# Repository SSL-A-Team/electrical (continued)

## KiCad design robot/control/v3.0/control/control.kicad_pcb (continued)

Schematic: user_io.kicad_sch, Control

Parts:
BZ1: MLT-5020
C32, C33, C34, C35, C36, C37: 0.1uF 63V; C_0402_1005Metric
C38: 4.7uF 25V; C_0805_2012Metric
D9: RBR5LAM60ATR; D_SOD-128
D10, D11, D12, D13: XL-1608UGC-04; LED0603
Q3: SI2310-TP; SOT-23
R84, R85, R86, R89, R90, R92, R93, R94, R95, R97, R107, R114, R115, R117: 330; R_0402_1005Metric
R87, R88, R96, R98, R99, R100, R101, R102, R103, R104, R105, R106, R108, R109, R110, R111, R112, R113, R116, R118: 10k; R_0402_1005Metric
R91: 10; R_0402_1005Metric
SW6: 219-8MST
SW7, SW8, SW9, SW10, SW11, SW12: B3F-1000
U4, U5, U6, U7, U8, U9, U10, U11, U12, U13, U14: SK9822

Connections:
+3V3: BZ1.1 (+), D9.1 (K), R87.2, R88.2, R106.2, R112.2, R113.2, R116.2, SW6.1, SW6.2, SW6.3, SW6.4, SW6.5, SW6.6, SW6.7, SW6.8; also elsewhere on the board
+5V: C38.2, U4.4 (VCC), U5.4 (VCC), U6.4 (VCC), U7.4 (VCC), U8.4 (VCC), U9.4 (VCC), U10.4 (VCC), U11.4 (VCC), U12.4 (VCC), U13.4 (VCC), U14.4 (VCC); also elsewhere on the board
/mcu/BTNS.BACK: R93.2; also elsewhere on the board
/mcu/BTNS.DOWN: R117.2; also elsewhere on the board
/mcu/BTNS.ENTER: R94.2; also elsewhere on the board
/mcu/BTNS.LEFT: R114.2; also elsewhere on the board
/mcu/BTNS.RIGHT: R115.2; also elsewhere on the board
/mcu/BTNS.UP: R107.2; also elsewhere on the board
/mcu/BUZZER: R91.1, R96.1; also elsewhere on the board
/mcu/DIP.0: R84.2; also elsewhere on the board
/mcu/DIP.1: R85.2; also elsewhere on the board
/mcu/DIP.2: R86.2; also elsewhere on the board
/mcu/DIP.3: R89.2; also elsewhere on the board
/mcu/DIP.4: R90.2; also elsewhere on the board
/mcu/DIP.5: R92.2; also elsewhere on the board
/mcu/DIP.6: R95.2; also elsewhere on the board
/mcu/DIP.7: R97.2; also elsewhere on the board
/mcu/DOTSTARS.MOSI: U4.1 (SDI); also elsewhere on the board
/mcu/DOTSTARS.SCK: R118.1, U4.2 (CKI); also elsewhere on the board
/mcu/LEDS.1: R111.1; also elsewhere on the board
/mcu/LEDS.2: R110.1; also elsewhere on the board
/mcu/LEDS.3: R109.1; also elsewhere on the board
/mcu/LEDS.4: R108.1; also elsewhere on the board
GND: C32.2, C33.2, C34.2, C35.2, C36.2, C37.2, C38.1, D10.1 (K), D11.1 (K), D12.1 (K), D13.1 (K), Q3.2 (S), R96.2, R98.1, R99.1, R100.1, R101.1, R102.1, R103.1, R104.1, R105.1, R118.2, SW7.3, SW8.3, SW9.3, SW10.3, SW11.3, SW12.3, U4.3 (GND), U5.3 (GND), U6.3 (GND), U7.3 (GND), U8.3 (GND), U9.3 (GND), U10.3 (GND), U11.3 (GND), U12.3 (GND), U13.3 (GND), U14.3 (GND); also elsewhere on the board
unnamed: BZ1.2 (-), D9.2 (A), Q3.3 (D)
unnamed: C32.1, R87.1, SW7.1
unnamed: C33.1, R88.1, SW8.1
unnamed: C34.1, R106.1, SW9.1
unnamed: C35.1, R112.1, SW10.1
unnamed: C36.1, R113.1, SW11.1
unnamed: C37.1, R116.1, SW12.1
unnamed: D10.2 (A), R108.2
unnamed: D11.2 (A), R109.2
unnamed: D12.2 (A), R110.2
unnamed: D13.2 (A), R111.2
unnamed: Q3.1 (G), R91.2
unnamed: R84.1, R98.2, SW6.16
unnamed: R85.1, R99.2, SW6.15
unnamed: R93.1, SW7.2
unnamed: R94.1, SW8.2
unnamed: R86.1, R100.2, SW6.14
unnamed: R89.1, R101.2, SW6.13
unnamed: R90.1, R102.2, SW6.12
unnamed: R92.1, R103.2, SW6.11
unnamed: R95.1, R104.2, SW6.10
unnamed: R97.1, R105.2, SW6.9
unnamed: R107.1, SW9.2
unnamed: R114.1, SW10.2
unnamed: R115.1, SW11.2
unnamed: R117.1, SW12.2
unnamed: U4.5 (CKO), U5.2 (CKI)
unnamed: U4.6 (SDO), U5.1 (SDI)
unnamed: U5.5 (CKO), U6.2 (CKI)
unnamed: U5.6 (SDO), U6.1 (SDI)
unnamed: U6.5 (CKO), U7.2 (CKI)
unnamed: U6.6 (SDO), U7.1 (SDI)
unnamed: U8.5 (CKO), U9.2 (CKI)
unnamed: U8.6 (SDO), U9.1 (SDI)
unnamed: U9.5 (CKO), U10.2 (CKI)
unnamed: U10.5 (CKO), U11.2 (CKI)
unnamed: U9.6 (SDO), U10.1 (SDI)
unnamed: U10.6 (SDO), U11.1 (SDI)
unnamed: U11.5 (CKO), U12.2 (CKI)
unnamed: U11.6 (SDO), U12.1 (SDI)
unnamed: U13.2 (CKI), U14.5 (CKO)
unnamed: U8.2 (CKI), U13.5 (CKO)
unnamed: U13.1 (SDI), U14.6 (SDO)
unnamed: U8.1 (SDI), U13.6 (SDO)
unnamed: U7.5 (CKO), U14.2 (CKI)
unnamed: U7.6 (SDO), U14.1 (SDI)

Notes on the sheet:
4x Motor 1x Radio 1x IMU 1x Kicker 1x Optical 1x Power 2x General Purpose
Dotstars
Robot Config
Debug Leds
Audio Indicators
User Buttons

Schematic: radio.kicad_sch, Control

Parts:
J5: BM10B-SRSS-TB; JST_SH_BM10B-SRSS-TB_1x10-1MP_P1.00mm_Vertical
R120, R121, R124, R125: 100k; R_0402_1005Metric
R122, R123: 330; R_0402_1005Metric

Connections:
+3V3: J5.9, R120.1, R121.1; also elsewhere on the board
+5V: J5.10; also elsewhere on the board
/mcu/ODIN.BOOT0: J5.7, R124.1; also elsewhere on the board
/mcu/ODIN.CTS: J5.4, R120.2; also elsewhere on the board
/mcu/ODIN.RTS: R123.1; also elsewhere on the board
/mcu/ODIN.RX: J5.5, R121.2; also elsewhere on the board
/mcu/ODIN.TX: R122.1; also elsewhere on the board
/mcu/ODIN.~DET: J5.2; also elsewhere on the board
/mcu/ODIN.~RST: J5.8, R125.1; also elsewhere on the board
GND: J5.1, J5.MP (MountPin), R124.2, R125.2; also elsewhere on the board
unnamed: J5.3, R123.2
unnamed: J5.6, R122.2

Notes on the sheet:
Radio Module Communication

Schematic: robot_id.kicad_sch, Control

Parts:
D3, D4, D6, D7: LTST-C195KGJRKT; LED0606_S_1324
D5: MHT194YBCT; LED0606_Z_1324
D8: XL-1608UOC-06; LED0603
J14: Conn_01x06; JST_GH_BM06B-GHS-TBT_1x06-1MP_P1.25mm_Vertical
R59, R60, R63, R64, R74, R75: 330; R_0402_1005Metric
R61, R62: 2.7k; R_0402_1005Metric
R65, R66, R67, R68, R69, R70, R71, R72, R73, R76, R77, R78, R79, R80, R81, R82, R83: 10k; R_0402_1005Metric
SW4: 221ADC16
SW5: SW_DIP_x02; 219-2MST

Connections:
+3V3: J14.1, R61.2, R62.2, R65.2, R66.2, R73.2, R79.2, R80.2, SW4.C, SW5.1, SW5.2; also elsewhere on the board
/mcu/BOT_ID_DISPLAY.BL: D6.2 (A2), D6.3 (K1); also elsewhere on the board
/mcu/BOT_ID_DISPLAY.BR: D7.2 (A2), D7.3 (K1); also elsewhere on the board
/mcu/BOT_ID_DISPLAY.FL: D3.2 (A2), D3.3 (K1); also elsewhere on the board
/mcu/BOT_ID_DISPLAY.FR: D4.2 (A2), D4.3 (K1); also elsewhere on the board
/mcu/BOT_ID_DISPLAY.SrcDisagree: R83.1; also elsewhere on the board
/mcu/BOT_ID_DISPLAY.TeamBlue: D5.2 (A2), D5.3 (K1); also elsewhere on the board
/mcu/BOT_ID_SWITCHES.IDX0: R64.2; also elsewhere on the board
/mcu/BOT_ID_SWITCHES.IDX1: R63.2; also elsewhere on the board
/mcu/BOT_ID_SWITCHES.IDX2: R60.2; also elsewhere on the board
/mcu/BOT_ID_SWITCHES.IDX3: R59.2; also elsewhere on the board
/mcu/BOT_ID_SWITCHES.SRC_PRIO_USER_~AUTO: R75.2; also elsewhere on the board
/mcu/BOT_ID_SWITCHES.TEAM_BLUE_~YELLOW: R74.2; also elsewhere on the board
/mcu/SHELL_DETECT.LIGHT: J14.5; also elsewhere on the board
/mcu/SHELL_DETECT.RST: J14.4; also elsewhere on the board
/mcu/SHELL_DETECT.SCL: J14.3, R62.1; also elsewhere on the board
/mcu/SHELL_DETECT.SDA: J14.2, R61.1; also elsewhere on the board
GND: D8.1 (K), J14.6, R67.1, R68.1, R69.1, R70.1, R71.1, R72.1, R76.1, R77.1, R78.1, R81.1, R82.1; also elsewhere on the board
unnamed: D3.1 (A1), R65.1
unnamed: D3.4 (K2), R71.2
unnamed: D4.1 (A1), R66.1
unnamed: D4.4 (K2), R72.2
unnamed: D5.1 (A1), R73.1
unnamed: D5.4 (K2), R76.2
unnamed: D6.1 (A1), R79.1
unnamed: D6.4 (K2), R81.2
unnamed: D7.1 (A1), R80.1
unnamed: D7.4 (K2), R82.2
unnamed: D8.2 (A), R83.2
unnamed: R64.1, R70.2, SW4.1
unnamed: R74.1, R77.2, SW5.4
unnamed: R75.1, R78.2, SW5.3
unnamed: R63.1, R69.2, SW4.4 (2)
unnamed: R60.1, R68.2, SW4.3 (4)
unnamed: R59.1, R67.2, SW4.6 (8)

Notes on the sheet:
Disagreement Warning
Dot Pattern Preview
Robot ID Selection
Shell ID Board Connector
Team Selection

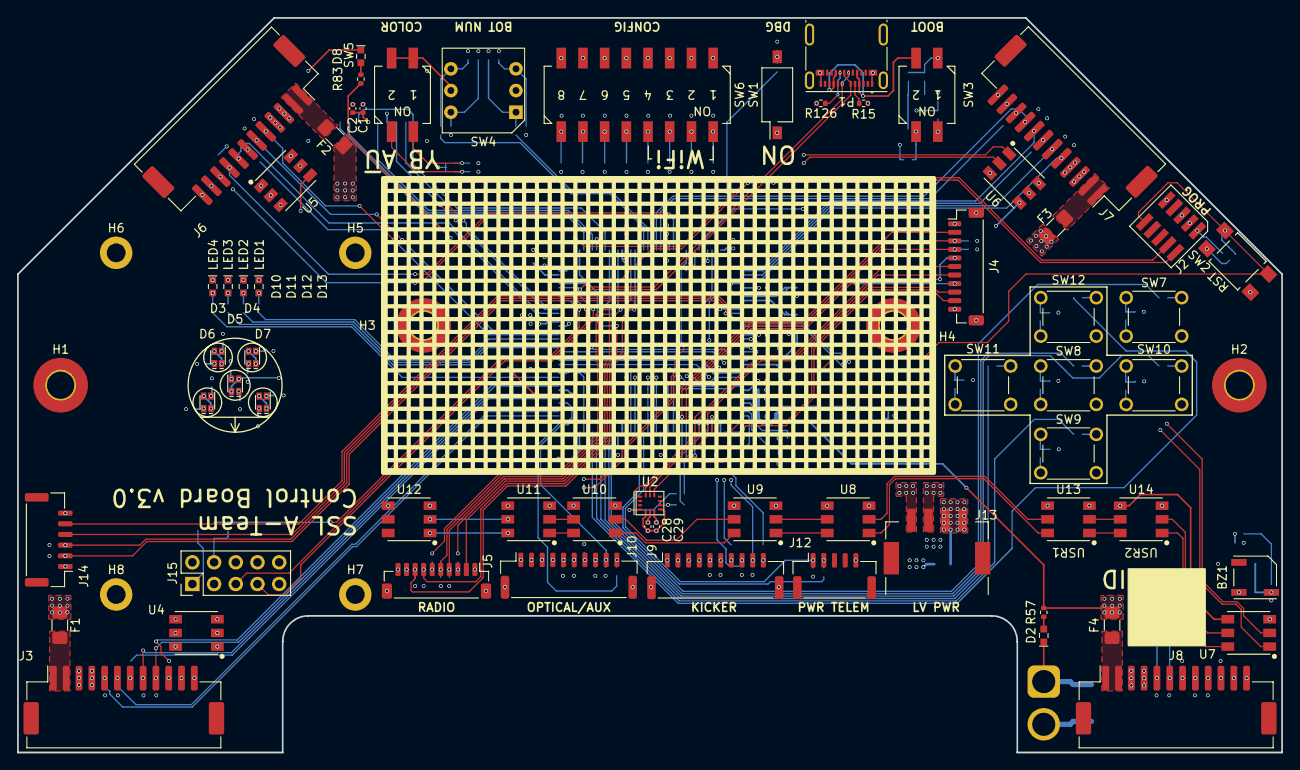
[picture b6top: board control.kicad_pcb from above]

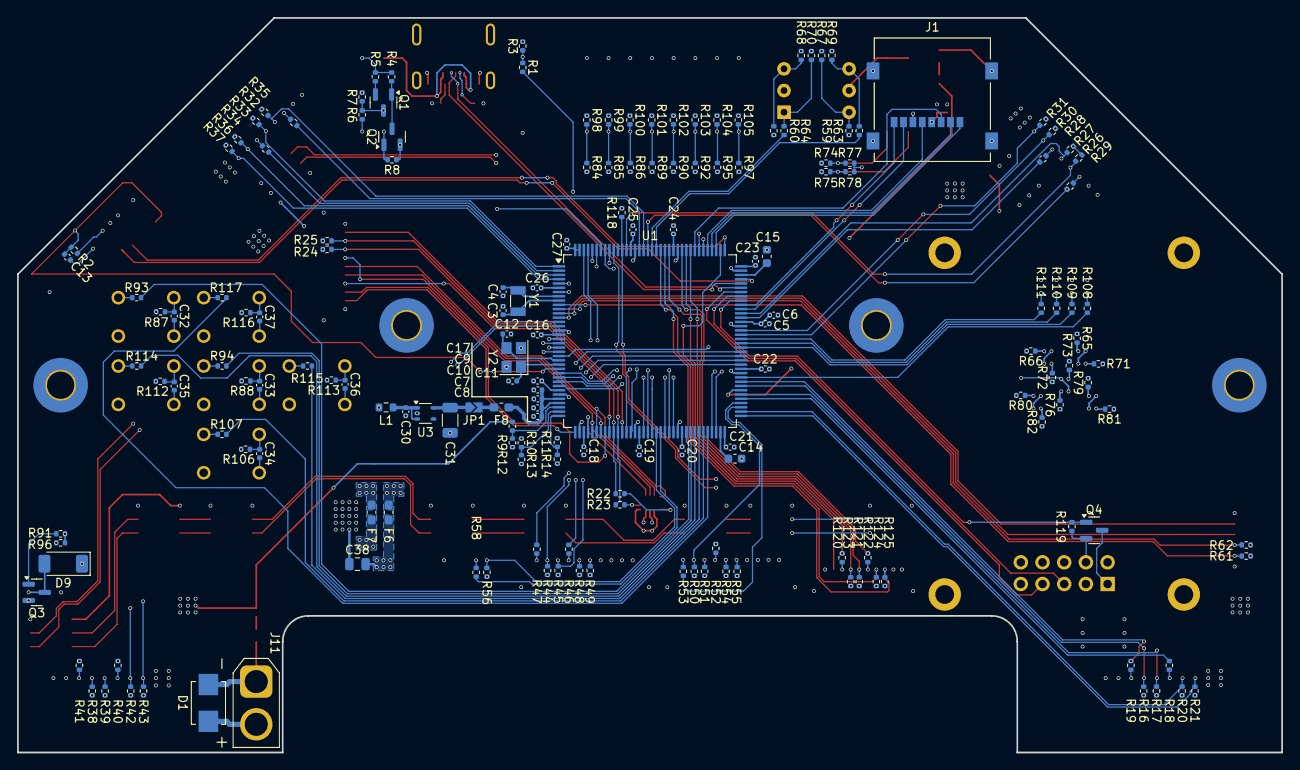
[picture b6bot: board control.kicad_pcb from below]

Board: 6 copper layers, 148.0 x 86.0 mm, 243 parts (173 on the bottom side), 221 nets.

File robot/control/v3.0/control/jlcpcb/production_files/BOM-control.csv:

Comment,Designator,Footprint,LCSC,Quantity
1k,"R12,R13,R14,R5,R6",R_0402_1005Metric,C11702,5
SMBJ26CA,D1,D_SMB_Non-Polar,C123932,1
LTST-C195KGJRKT,"D3,D4,D6,D7",LED0606_S_1324,C125104,4
USB_C_Plug_USB2.0,P1,USB_C_Receptacle_Molex_105450-0101,C134092,1
1u 50V,"C2,C6,C8,C9",C_0402_1005Metric,C1518208,4
650 @100MHz,L1,R_0603_1608Metric,C15402,1
15pF,"C3,C4",C_0402_1005Metric,C1548,2
2.2uF 10V,"C14,C15",C_0603_1608Metric,C1607,2
11pF,"C11,C12",C_0402_1005Metric,C161525,2
0.1uF 63V,"C28,C29,C30,C32,C33,C34,C35,C36,C37",C_0402_1005Metric,C162178,9
4.7uF 25V,C38,C_0805_2012Metric,C1779,1
1u,C31,C_1206_3216Metric,C1848,1
Conn_01x06,J14,JST_GH_BM06B-GHS-TBT_1x06-1MP_P1.25mm_Vertical,C189892,1
JST-GH-SM05B,J12,JST_GH_SM05B-GHS-TB_1x05-1MP_P1.25mm_Horizontal,C189896,1
10,R91,R_0402_1005Metric,C25077,1
330,"R1,R107,R114,R115,R117,R122,R123,R18,R19,R22,R23,R28,R29,R34,R35,R40,R41,R46,R47,R52,R53,R58,R59,R60,R63,R64,R74,R75,R84,R85,R86,R89,R90,R92,R93,R94,R95,R97",R_0402_1005Metric,C25104,38
BSS138K,"Q2,Q4",SOT-23,C255592,2
100k,"R119,R120,R121,R124,R125,R16,R17,R20,R21,R26,R27,R30,R31,R32,R33,R36,R37,R38,R39,R4,R42,R43,R44,R45,R48,R49,R50,R51,R54,R55,R56,R7,R8",R_0402_1005Metric,C25741,33
10k,"R100,R101,R102,R103,R104,R105,R106,R108,R109,R110,R111,R112,R113,R116,R118,R24,R25,R3,R65,R66,R67,R68,R69,R70,R71,R72,R73,R76,R77,R78,R79,R80,R81,R82,R83,R87,R88,R96,R98,R99",R_0402_1005Metric,C25744,40
1.5k,R10,R_0402_1005Metric,C25867,1
2.7k,"R61,R62",R_0402_1005Metric,C25885,2
5.1k,"R126,R15",R_0402_1005Metric,C25905,2
Conn_01x04,J13,JST_PA_SM04B-PASS_1x04_P2.00mm_Horizontal,C265073,1
BM10B-SRSS-TB,J5,JST_SH_BM10B-SRSS-TB_1x10-1MP_P1.00mm_Vertical,C265443,1
Conn_01x10_MountingPin,"J10,J9",JST_GH_SM10B-GHS-TB_1x10-1MP_P1.25mm_Horizontal,C2683602,2
11.5k,R9,R_0402_1005Metric,C270653,1
MHT194YBCT,D5,LED0606_Z_1324,C2764891,1
SK9822,"U10,U11,U12,U13,U14,U4,U5,U6,U7,U8,U9",SK9822,C2829089,11
219-8MST,SW6,219-8MST,C2842674,1
RST,SW2,SW_SPST_TL3305A,C2886902,1
~,"F6,F7",Fuse_0603_1608Metric_Pad1.05x0.95mm_HandSolder,C2924957,2
SW_DIP_x02,SW3,219-2MST,C2961978,1
SW_DIP_x02,SW5,219-2MST,C314502,1
23.7k,R57,R_0402_1005Metric,C327362,1
06F-0200L1,F8,Fuse_0603_1608Metric_Pad1.05x0.95mm_HandSolder,C377220,1
TAXM8M4RDBCCT2T,Y2,Crystal_SMD_3225-4Pin_3.2x2.5mm,C400090,1
Conn_ARM_JTAG_SWD_10,J2,Samtec-2x5pin-1.27mm,C448647,1
RBR5LAM60ATR,D9,D_SOD-128,C509955,1
TLV70030_SOT353,U3,SOT-353_SC-70-5,C527437,1
BMI323,U2,BMI323,C5368700,1
4A,"F1,F2,F3,F4",Fuse_1206_3216Metric_Pad1.42x1.75mm_HandSolder,C5383193,4
A6SN-1104,SW1,SW_DIP_SPSTx01_Slide_Omron_A6S-110x_W8.9mm_P2.54mm,C600988,1
SI2310-TP,Q3,SOT-23,C669000,1
STM32H723ZGTx,U1,LQFP-144_20x20mm_P0.5mm,C730146,1
100n 50V,"C1,C10,C13,C16,C17,C18,C19,C20,C21,C22,C23,C24,C25,C26,C27,C5,C7",C_0402_1005Metric,C77020,17
650,R11,R_0402_1005Metric,C82294,1
Q13FC13500005,Y1,Crystal_SMD_3215-2Pin_3.2x1.5mm,C841881,1
BSS84,Q1,SOT-23,C85202,1
B3F-1000,"SW10,SW11,SW12,SW7,SW8,SW9",B3F-1000,C93157,6
MLT-5020,BZ1,MLT-5020,C95297,1
XL-1608UOC-06,D8,LED0603,C965800,1
XL-1608UGC-04,"D10,D11,D12,D13",LED0603,C965804,4
XL-1608UWC-04,D2,LED0603,C965808,1
SM12B-ZESS,J6,JST_ZE_SM12B-ZESS-TB_1x12-1MP_P1.50mm_Horizontal,,1
221ADC16,SW4,221ADC16,,1
SM12B-ZESS,J8,JST_ZE_SM12B-ZESS-TB_1x12-1MP_P1.50mm_Horizontal,,1
SM12B-ZESS,J3,JST_ZE_SM12B-ZESS-TB_1x12-1MP_P1.50mm_Horizontal,,1
SM12B-ZESS,J7,JST_ZE_SM12B-ZESS-TB_1x12-1MP_P1.50mm_Horizontal,,1
BM11B-SRSS-TB,J4,JST_SH_BM11B-SRSS-TB_1x11-1MP_P1.00mm_Vertical,,1
Conn_02x05_Odd_Even,J15,PinHeader_2x05_P2.54mm_Vertical,,1
MEM2067-02-180-00-A,J1,MEM2067-02-180-00-A,,1

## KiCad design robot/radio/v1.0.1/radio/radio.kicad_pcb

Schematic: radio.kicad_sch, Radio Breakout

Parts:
C1, C2, C10, C11: 10u 10v; C_0603_1608Metric
C3: 1u 10v; C_0603_1608Metric
C4: 0.1u 10v; C_0603_1608Metric
C5, C6, C7, C8, C9: 0.1u; C_0603_1608Metric
D1: 150141m173100; LED_RGB_Wuerth-PLCC4_3.2x2.8mm_150141M173100
H1, H2: MountingHole; MountingHole_3.2mm_M3
J1: Conn_01x10; JST_SH_SM10B-SRSS-TB_1x10-1MP_P1.00mm_Horizontal
JP1: SW1; SolderJumper-2_2.0x1.2mm_Open
JP2: SW0; SolderJumper-2_2.0x1.2mm_Open
JP3: RTS Source Select; SolderJumper-3_P1.3mm_Open_RoundedPad1.0x1.5mm
JP4: CTS Source Select; SolderJumper-3_P1.3mm_Open_RoundedPad1.0x1.5mm
Q1: BSS138K; SOT-23
R1, R3: 1k; R_0603_1608Metric
R2: 2K7; R_0603_1608Metric
R4, R5: 330; R_0603_1608Metric
R6, R7, R8, R9, R10: 10k; R_0603_1608Metric
SW1: SPST_12-34; TS02-66-73-BK-160-SCR-D
U1: 74LVC3G07; VSSOP-8_2.3x2mm_P0.5mm
U2: ODIN-W26x; ODIN_W2
U3: TXS0108EPW; TSSOP-20_4.4x6.5mm_P0.65mm

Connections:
+1V8: C5.2, C7.2, R6.2, R10.2, U1.8 (VCC), U2.A2 (V_INT), U3.2 (VCCA)
+3V3: C1.2, C2.2, C3.2, C4.2, C6.2, C10.2, C11.2, D1.1 (A), J1.9, U2.A4 (VCC), U3.19 (VCCB)
+5V: J1.10
/BLUE: U1.1, U2.A9 (BLUE)
/BLUE_B: R3.1, U1.7
/BOOT0_3v3: J1.7
/GRN_B: R2.1, U1.2
/GRN_SW1: R4.2, U1.6, U2.A8 (GREEN/SWITCH_1)
/LED_B_CL: D1.2 (BK), R3.2
/LED_G_CL: D1.4 (GK), R2.2
/LED_R_CL: D1.3 (RK), R1.2
/RADIO_CTS_3v3: JP4.2 (C), U3.18 (B2)
/RADIO_RTS_3v3: JP3.2 (C), U3.20 (B1)
/RED: U1.3, U2.A7 (RED)
/RED_B: R1.1, U1.5
/RESET_N: C9.2, Q1.3 (D), SW1.1, U2.A1 (RESET_N)
/RST_3v3: J1.8, Q1.1 (G), R8.2
/SW0: R5.1, U2.A6 (SWITCH_0)
/UART_CTS_1v8: U2.A10 (UART_CTS), U3.3 (A2)
/UART_CTS_3v3: J1.4, JP3.1 (A), JP4.1 (A)
/UART_RTS_1v8: U2.A12 (UART_RTS), U3.1 (A1)
/UART_RTS_3v3: J1.3, JP3.3 (B), JP4.3 (B)
/UART_RX_1v8: U2.A13 (UART_RXD), U3.4 (A3)
/UART_RX_3v3: J1.6, U3.17 (B3)
/UART_TX_1v8: U2.A11 (UART_TXD), U3.5 (A4)
/UART_TX_3v3: J1.5, U3.16 (B4)
GND: C1.1, C2.1, C3.1, C4.1, C5.1, C6.1, C7.1, C8.2, C9.1, C10.1, C11.1, J1.1, J1.2, JP1.2 (B), JP2.2 (B), Q1.2 (S), R6.1, R7.1, R8.1, R9.1, SW1.4, U1.4 (GND), U2.A3 (GND), U2.C1 (GND), U2.C3 (GND), U2.C4 (GND), U2.C7 (GND), U2.D7 (GND), U2.G1 (GND), U2.G2 (GND), U2.G3 (GND), U2.G4 (GND), U2.G5 (GND), U2.G6 (GND), U2.G7 (GND), U2.G8 (GND), U2.G9 (GND), U2.G10 (GND), U2.G11 (GND), U2.G12 (GND), U2.G13 (GND), U2.G14 (GND), U2.G15 (GND), U2.G16 (GND), U2.G17 (GND), U2.G18 (GND), U2.G19 (GND), U2.G20 (GND), U2.G21 (GND), U2.G22 (GND), U2.G23 (GND), U2.G24 (GND), U2.G25 (GND), U2.G26 (GND), U2.G27 (GND), U2.G28 (GND), U2.G29 (GND), U2.G30 (GND), U2.G31 (GND), U2.G32 (GND), U2.G33 (GND), U2.G34 (GND), U2.G35 (GND), U2.G36 (GND), U2.G37 (GND), U2.G38 (GND), U2.G39 (GND), U3.11 (GND)
unnamed: JP1.1 (A), R4.1
unnamed: JP2.1 (A), R5.2
unnamed: R7.2, U3.6 (A5), U3.7 (A6), U3.8 (A7), U3.9 (A8)
unnamed: R9.2, U3.12 (B8), U3.13 (B7), U3.14 (B6), U3.15 (B5)
unnamed: C8.1, R10.1, U3.10 (OE)

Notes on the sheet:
Radio Ground
~{DET}
Radio Pinout
Green signal will not be valid until 500ms after startup
Level Shifter
Board Reset
Decoupling cap for 74LVC
Status LEDs
UART/Firmware Reset
Bridge SW1 and power on to restore UART defaults Bridge SW1 and SW0 and power on for 10s to restore all factory defaults

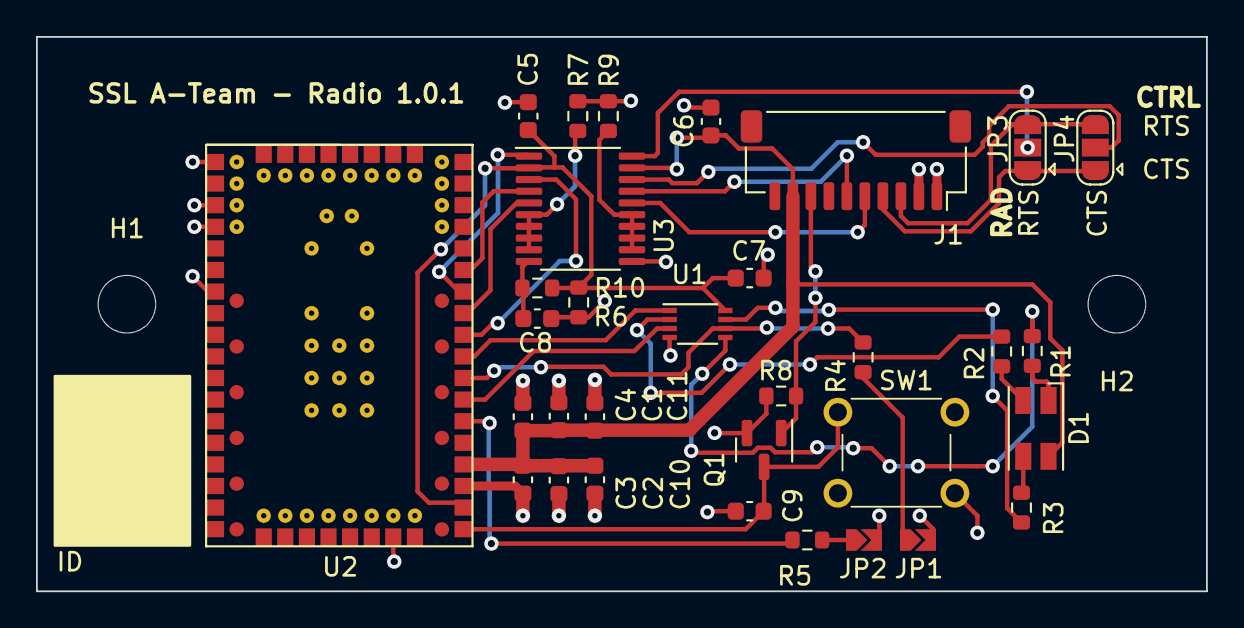
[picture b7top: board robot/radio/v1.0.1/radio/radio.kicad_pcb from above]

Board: 2 copper layers, 65.0 x 30.8 mm, 34 parts (0 on the bottom side), 30 nets.

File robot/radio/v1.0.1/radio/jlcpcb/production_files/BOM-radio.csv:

Comment,Designator,Footprint,LCSC,Quantity
74LVC3G07,U1,VSSOP-8_2.3x2mm_P0.5mm,C131955,1
0.1u 10v,"C4,C5,C6,C7,C8,C9",C_0603_1608Metric,C1591,6
Conn_01x10,J1,JST_SH_SM10B-SRSS-TB_1x10-1MP_P1.00mm_Horizontal,C160409,1
TXS0108EPW,U3,TSSOP-20_4.4x6.5mm_P0.65mm,C17206,1
10u 10v,"C1,C10,C11,C2",C_0603_1608Metric,C19702,4
1k,"R1,R3",R_0603_1608Metric,C21190,2
330,"R4,R5",R_0603_1608Metric,C23138,2
BSS138K,Q1,SOT-23,C255592,1
10k,"R10,R6,R7,R8,R9",R_0603_1608Metric,C25804,5
1u 10v,C3,C_0603_1608Metric,C26413,1
2K7,R2,R_0603_1608Metric,C328353,1
150141m173100,D1,LED_RGB_Wuerth-PLCC4_3.2x2.8mm_150141M173100,C5342281,1

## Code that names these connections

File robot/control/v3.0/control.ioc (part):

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Mcu.Name=STM32H723ZGTx
Mcu.Package=LQFP144
Mcu.UserName=STM32H723ZGTx
PA0.GPIOParameters=GPIO_Label
PA0.GPIO_Label=ADC1_INP16_VBATT
PA0.Mode=IN16-Single-Ended
PA0.Signal=ADC1_INP16
PA1.GPIOParameters=GPIO_Label
PA1.GPIO_Label=ADC1_INP17_5v0
PA1.Mode=IN17-Single-Ended
PA1.Signal=ADC1_INP17
PA10.GPIOParameters=GPIO_Label
PA10.GPIO_Label=USART1_RX_DISPLAY
PA10.Mode=Asynchronous
PA10.Signal=USART1_RX
PA11.Mode=Device_Only_FS
PA11.Signal=USB_OTG_HS_DM
PA12.Mode=Device_Only_FS
PA12.Signal=USB_OTG_HS_DP
PA13(JTMS/SWDIO).Mode=Serial_Wire
PA13(JTMS/SWDIO).Signal=DEBUG_JTMS-SWDIO
PA14(JTCK/SWCLK).Mode=Serial_Wire
PA14(JTCK/SWCLK).Signal=DEBUG_JTCK-SWCLK
PA15(JTDI).GPIOParameters=GPIO_Label
PA15(JTDI).GPIO_Label=PA15_RADIO_nDET
PA15(JTDI).Signal=GPIO_Input
PA2.GPIOParameters=GPIO_Label
PA2.GPIO_Label=ADC1_INP14_3v3
PA2.Signal=ADCx_INP14
PA3.GPIOParameters=GPIO_Label
PA3.GPIO_Label=PA3_IMU_NSS1
PA3.Signal=GPIO_Output
PA4.GPIOParameters=GPIO_Label
PA4.GPIO_Label=SPI1_NSS0_IMU
PA4.Mode=NSS_Signal_Hard_Input
PA4.Signal=SPI1_NSS
PA5.GPIOParameters=GPIO_Label
PA5.GPIO_Label=SPI1_SCK_IMU
PA5.Mode=Full_Duplex_Master
PA5.Signal=SPI1_SCK
PA6.GPIOParameters=GPIO_Label
PA6.GPIO_Label=SPI1_MISO_IMU
PA6.Mode=Full_Duplex_Master
PA6.Signal=SPI1_MISO
PA7.GPIOParameters=GPIO_Label
PA7.GPIO_Label=SPI1_MOSI_IMU
PA7.Mode=Full_Duplex_Master
PA7.Signal=SPI1_MOSI
PA8.GPIOParameters=GPIO_Label
PA8.GPIO_Label=O_DISPLAY_RST
PA8.Signal=GPIO_Output
PA9.GPIOParameters=GPIO_Label
PA9.GPIO_Label=USART1_TX_DISPLAY
PA9.Mode=Asynchronous
PA9.Signal=USART1_TX
PB0.GPIOParameters=GPIO_Label
PB0.GPIO_Label=EXTI0_IMU_INT1
PB0.Signal=GPXTI0
PB1.GPIOParameters=GPIO_Label
PB1.GPIO_Label=EXTI1_IMU_INT2
PB1.Signal=GPXTI1
PB10.GPIOParameters=GPIO_Label
PB10.GPIO_Label=BOT_ID_TEAM
PB10.Signal=GPIO_Input
PB11.GPIOParameters=GPIO_Label
PB11.GPIO_Label=BOT_ID_SRC_PRIO
PB11.Signal=GPIO_Input
PB12.GPIOParameters=GPIO_Label
PB12.GPIO_Label=PB12_MOTOR_FR_BOOT0
PB12.Signal=GPIO_Output
PB13.GPIOParameters=GPIO_Label
PB13.GPIO_Label=PB13_MOTOR_FR_RST
PB13.Signal=GPIO_Output
PB14.GPIOParameters=GPIO_Label
PB14.GPIO_Label=UART4_RTS_FLOWCONTROL
PB14.Mode=CTS_RTS
PB14.Signal=UART4_RTS
PB15.GPIOParameters=GPIO_Label
PB15.GPIO_Label=UART4_CTS_FLOWCONTROL
PB15.Mode=CTS_RTS
PB15.Signal=UART4_CTS
PB2.GPIOParameters=GPIO_Label
PB2.GPIO_Label=PB2_IMU_NDET
PB2.Signal=GPIO_Input
PB3(JTDO/TRACESWO).GPIOParameters=GPIO_Label
PB3(JTDO/TRACESWO).GPIO_Label=SPI6_SCK_DOTSTAR
PB3(JTDO/TRACESWO).Mode=Full_Duplex_Master
PB3(JTDO/TRACESWO).Signal=SPI6_SCK
PB4(NJTRST).GPIOParameters=GPIO_Label
PB4(NJTRST).GPIO_Label=SPI6_MISO_DOTSTAR
PB4(NJTRST).Mode=Full_Duplex_Master
PB4(NJTRST).Signal=SPI6_MISO
PB5.GPIOParameters=GPIO_Label
PB5.GPIO_Label=SPI6_MOSI_DOTSTAR
PB5.Mode=Full_Duplex_Master
PB5.Signal=SPI6_MOSI
PB6.GPIOParameters=GPIO_Label
PB6.GPIO_Label=PB7_FLOWCONTROL_RST
PB6.Signal=GPIO_Output
PB7.GPIOParameters=GPIO_Label
PB7.GPIO_Label=PB7_FLOWCONTROL_BOOT0
PB7.Signal=GPIO_Output
PB8.GPIOParameters=GPIO_Label
PB8.GPIO_Label=UART4_RX_FLOWCONTROL
PB8.Mode=Asynchronous
PB8.Signal=UART4_RX
PB9.GPIOParameters=GPIO_Label
PB9.GPIO_Label=UART4_TX_FLOWCONTROL
PB9.Mode=Asynchronous
PB9.Signal=UART4_TX
PC0.GPIOParameters=GPIO_Label
PC0.GPIO_Label=BOT_ID_IND_FL
PC0.Signal=GPIO_Output
PC1.GPIOParameters=GPIO_Label
PC1.GPIO_Label=BOT_ID_IND_FR
PC1.Signal=GPIO_Output
PC10.Mode=SD_4_bits_Wide_bus
PC10.Signal=SDMMC1_D2
PC11.Mode=SD_4_bits_Wide_bus
PC11.Signal=SDMMC1_D3
PC12.Mode=SD_4_bits_Wide_bus
PC12.Signal=SDMMC1_CK
PC13.GPIOParameters=GPIO_Label
PC13.GPIO_Label=DIP_DEBUG_MODE
PC13.Signal=GPIO_Input
PC14-OSC32_IN.Mode=LSE-External-Oscillator
PC14-OSC32_IN.Signal=RCC_OSC32_IN
PC15-OSC32_OUT.Mode=LSE-External-Oscillator
PC15-OSC32_OUT.Signal=RCC_OSC32_OUT
PC2_C.GPIOParameters=GPIO_Label
PC2_C.GPIO_Label=BOT_ID_IND_BL
PC2_C.Signal=GPIO_Output
PC3_C.GPIOParameters=GPIO_Label
PC3_C.GPIO_Label=BOT_ID_IND_BR
PC3_C.Signal=GPIO_Output
PC4.GPIOParameters=GPIO_Label
PC4.GPIO_Label=PC4_IMU_NSS2
PC4.Signal=GPIO_Output
PC5.GPIOParameters=GPIO_Label
PC5.GPIO_Label=PC5_IMU_NSS3
PC5.Signal=GPIO_Output
PC6.GPIOParameters=GPIO_Label
PC6.GPIO_Label=USART6_TX_MOTOR_BR
PC6.Mode=Asynchronous
PC6.Signal=USART6_TX
PC7.GPIOParameters=GPIO_Label
PC7.GPIO_Label=USART6_RX_MOTOR_BR
PC7.Mode=Asynchronous
PC7.Signal=USART6_RX
PC8.Mode=SD_4_bits_Wide_bus
PC8.Signal=SDMMC1_D0
PC9.Mode=SD_4_bits_Wide_bus
PC9.Signal=SDMMC1_D1
PD0.GPIOParameters=GPIO_Label
PD0.GPIO_Label=BOT_ID_3
PD0.Signal=GPIO_Input
PD1.GPIOParameters=GPIO_Label
PD1.GPIO_Label=BOT_ID_2
PD1.Signal=GPIO_Input
PD10.GPIOParameters=GPIO_Label
PD10.GPIO_Label=BOT_ID_SRC_DISAGREE
PD10.Signal=GPIO_Output
PD11.GPIOParameters=GPIO_Label
PD11.GPIO_Label=USART3_CTS_MOTOR_FR
PD11.Mode=CTS_RTS
PD11.Signal=USART3_CTS
PD12.GPIOParameters=GPIO_Label
PD12.GPIO_Label=USART3_RTS_MOTOR_FR
PD12.Mode=CTS_RTS
PD12.Signal=USART3_RTS
PD13.GPIOParameters=GPIO_Label
PD13.GPIO_Label=LED4
PD13.Signal=GPIO_Output
PD14.GPIOParameters=GPIO_Label
PD14.GPIO_Label=UART8_CTS_KICKER
PD14.Mode=CTS_RTS
PD14.Signal=UART8_CTS
PD15.GPIOParameters=GPIO_Label
PD15.GPIO_Label=UART8_RTS_KICKER
PD15.Mode=CTS_RTS
PD15.Signal=UART8_RTS
PD2.Mode=SD_4_bits_Wide_bus
PD2.Signal=SDMMC1_CMD
PD3.GPIOParameters=GPIO_Label
PD3.GPIO_Label=USART2_CTS_RADIO
PD3.Mode=CTS_RTS
PD3.Signal=USART2_CTS
PD4.GPIOParameters=GPIO_Label
PD4.GPIO_Label=USART2_RTS_RADIO
PD4.Mode=CTS_RTS
PD4.Signal=USART2_RTS
PD5.GPIOParameters=GPIO_Label
PD5.GPIO_Label=USART2_TX_RADIO
PD5.Mode=Asynchronous
PD5.Signal=USART2_TX
PD6.GPIOParameters=GPIO_Label
PD6.GPIO_Label=USART2_RX_RADIO
PD6.Mode=Asynchronous
PD6.Signal=USART2_RX
PD7.GPIOParameters=GPIO_Label
PD7.GPIO_Label=PD7_RADIO_RST
PD7.Signal=GPIO_Output
PD8.GPIOParameters=GPIO_Label
PD8.GPIO_Label=USART3_TX_MOTOR_FR
PD8.Mode=Asynchronous
PD8.Signal=USART3_TX
PD9.GPIOParameters=GPIO_Label
PD9.GPIO_Label=USART3_RX_MOTOR_FR
PD9.Mode=Asynchronous
PD9.Signal=USART3_RX
PE0.GPIOParameters=GPIO_Label
PE0.GPIO_Label=UART8_RX_KICKER
PE0.Mode=Asynchronous
PE0.Signal=UART8_RX
PE1.GPIOParameters=GPIO_Label
PE1.GPIO_Label=UART8_TX_KICKER
PE1.Mode=Asynchronous
PE1.Signal=UART8_TX
PE10.GPIOParameters=GPIO_Label
PE10.GPIO_Label=PE10_EXTI10_BTN_BACK
PE10.Signal=GPXTI10
PE11.GPIOParameters=GPIO_Label
PE11.GPIO_Label=PE11_EXTI11_BTN_ENTER
PE11.Signal=GPXTI11
PE12.GPIOParameters=GPIO_Label
PE12.GPIO_Label=PE12_EXTI12_BTN_LEFT
PE12.Signal=GPXTI12
PE13.GPIOParameters=GPIO_Label
PE13.GPIO_Label=PE13_EXTI13_BTN_RIGHT
PE13.Signal=GPXTI13
PE14.GPIOParameters=GPIO_Label
PE14.GPIO_Label=PE14_EXTI14_BTN_UP
PE14.Signal=GPXTI14
PE15.GPIOParameters=GPIO_Label
PE15.GPIO_Label=PE15_EXTI15_BTN_DOWN
PE15.Signal=GPXTI15
PE2.GPIOParameters=GPIO_Label
PE2.GPIO_Label=USART10_RX_MOTOR_BL
PE2.Mode=Asynchronous
PE2.Signal=USART10_RX
PE3.GPIOParameters=GPIO_Label
PE3.GPIO_Label=USART10_TX_MOTOR_BL
PE3.Mode=Asynchronous
PE3.Signal=USART10_TX
PE4.GPIOParameters=GPIO_Label
PE4.GPIO_Label=PE4_MOTOR_BL_RST
PE4.Signal=GPIO_Output
PE5.GPIOParameters=GPIO_Label
PE5.GPIO_Label=PE5_MOTOR_BL_BOOT0
PE5.Signal=GPIO_Output
PE6.GPIOParameters=GPIO_Label
PE6.GPIO_Label=TIM15_CH2_BUZZER
PE6.Signal=S_TIM15_CH2
PE7.GPIOParameters=GPIO_Label
PE7.GPIO_Label=DIP5
PE7.Signal=GPIO_Input
PE8.GPIOParameters=GPIO_Label
PE8.GPIO_Label=DIP6
PE8.Signal=GPIO_Input
PE9.GPIOParameters=GPIO_Label
PE9.GPIO_Label=DIP7
PE9.Signal=GPIO_Input
PF0.GPIOParameters=GPIO_Label
PF0.GPIO_Label=I2C2_SDA_SHELL_DET
PF0.Mode=I2C
PF0.Signal=I2C2_SDA
PF1.GPIOParameters=GPIO_Label
PF1.GPIO_Label=I2C2_SCL_SHELL_DET
PF1.Mode=I2C
PF1.Signal=I2C2_SCL
PF10.GPIOParameters=GPIO_Label
PF10.GPIO_Label=BOT_ID_IND_TEAM
PF10.Signal=GPIO_Output
PF11.GPIOParameters=GPIO_Label
PF11.GPIO_Label=DIP0
PF11.Signal=GPIO_Input
PF12.GPIOParameters=GPIO_Label
PF12.GPIO_Label=DIP1
PF12.Signal=GPIO_Input
PF13.GPIOParameters=GPIO_Label
PF13.GPIO_Label=DIP2
PF13.Signal=GPIO_Input
PF14.GPIOParameters=GPIO_Label
PF14.GPIO_Label=DIP3
PF14.Signal=GPIO_Input
PF15.GPIOParameters=GPIO_Label
PF15.GPIO_Label=DIP4
PF15.Signal=GPIO_Input
PF2.GPIOParameters=GPIO_Label
PF2.GPIO_Label=O_SHELL_DET_RST
PF2.Signal=GPIO_Output
PF3.GPIOParameters=GPIO_Label
PF3.GPIO_Label=O_SHELL_DET_BACKLIGHT
PF3.Signal=GPIO_Output
PF4.GPIOParameters=GPIO_Label
PF4.GPIO_Label=PF4_MOTOR_FL_RST
PF4.Signal=GPIO_Output
PF5.GPIOParameters=GPIO_Label
PF5.GPIO_Label=PF5_MOTOR_FL_BOOT0
PF5.Signal=GPIO_Output
PF6.GPIOParameters=GPIO_Label
PF6.GPIO_Label=UART7_RX_MOTOR_FL
PF6.Mode=Asynchronous
PF6.Signal=UART7_RX
PF7.GPIOParameters=GPIO_Label
PF7.GPIO_Label=UART7_TX_MOTOR_FL
PF7.Mode=Asynchronous
PF7.Signal=UART7_TX
PF8.GPIOParameters=GPIO_Label
PF8.GPIO_Label=UART7_RTS_MOTOR_FL
PF8.Mode=CTS_RTS
PF8.Signal=UART7_RTS
PF9.GPIOParameters=GPIO_Label
PF9.GPIO_Label=UART7_CTS_MOTOR_FL
PF9.Mode=CTS_RTS
PF9.Signal=UART7_CTS
PG0.GPIOParameters=GPIO_Label
PG0.GPIO_Label=UART9_RX_POWER
PG0.Mode=Asynchronous
PG0.Signal=UART9_RX
PG1.GPIOParameters=GPIO_Label
PG1.GPIO_Label=UART9_TX_POWER
PG1.Mode=Asynchronous
PG1.Signal=UART9_TX
PG10.GPIOParameters=GPIO_Label
PG10.GPIO_Label=BOT_ID_1
PG10.Signal=GPIO_Input

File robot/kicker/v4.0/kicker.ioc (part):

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Mcu.Name=STM32G474V(B-C-E)Tx
Mcu.Package=LQFP100
Mcu.UserName=STM32G474VETx
PA0.GPIOParameters=GPIO_Label
PA0.GPIO_Label=SENSE_VBATT
PA0.Mode=IN1-Single-Ended
PA0.Signal=ADC1_IN1
PA1.GPIOParameters=GPIO_Label
PA1.GPIO_Label=SENSE_VSW
PA1.Mode=IN2-Single-Ended
PA1.Signal=ADC1_IN2
PA10.GPIOParameters=GPIO_Label
PA10.GPIO_Label=BOOT_USART1_RX
PA10.Mode=Asynchronous
PA10.Signal=USART1_RX
PA11.GPIOParameters=GPIO_Label
PA11.GPIO_Label=BOOT_USART1_CTS
PA11.Mode=CTS_RTS
PA11.Signal=USART1_CTS
PA12.GPIOParameters=GPIO_Label
PA12.GPIO_Label=BOOT_USART1_RTS
PA12.Mode=CTS_RTS
PA12.Signal=USART1_RTS
PA13.Mode=Serial_Wire
PA13.Signal=SYS_JTMS-SWDIO
PA14.Mode=Serial_Wire
PA14.Signal=SYS_JTCK-SWCLK
PA15.Mode=I2C
PA15.Signal=I2C1_SCL
PA2.GPIOParameters=GPIO_Label
PA2.GPIO_Label=SENSE_5V
PA2.Mode=IN3-Single-Ended
PA2.Signal=ADC1_IN3
PA3.GPIOParameters=GPIO_Label
PA3.GPIO_Label=SENSE_3V3
PA3.Mode=IN4-Single-Ended
PA3.Signal=ADC1_IN4
PA4.GPIOParameters=GPIO_Label
PA4.GPIO_Label=FLASH_SPI1_NSS
PA4.Mode=NSS_Signal_Hard_Input
PA4.Signal=SPI1_NSS
PA5.GPIOParameters=GPIO_Label
PA5.GPIO_Label=FLASH_SPI1_SCK
PA5.Mode=Full_Duplex_Master
PA5.Signal=SPI1_SCK
PA6.GPIOParameters=GPIO_Label
PA6.GPIO_Label=FLASH_SPI1_MISO
PA6.Mode=Full_Duplex_Master
PA6.Signal=SPI1_MISO
PA7.GPIOParameters=GPIO_Label
PA7.GPIO_Label=FLASH_SPI1_MOSI
PA7.Mode=Full_Duplex_Master
PA7.Signal=SPI1_MOSI
PA9.GPIOParameters=GPIO_Label
PA9.GPIO_Label=BOOT_USART1_TX
PA9.Mode=Asynchronous
PA9.Signal=USART1_TX
PB0.Mode=PGA_Internally_Connected
PB0.Signal=OPAMP3_VINP
PB1.Signal=OPAMP3_VOUT
PB10.GPIOParameters=GPIO_Label
PB10.GPIO_Label=DRIBBLER_USART3_TX
PB10.Mode=Asynchronous
PB10.Signal=USART3_TX
PB13.GPIOParameters=GPIO_Label
PB13.GPIO_Label=DRIBBLER_USART3_CTS
PB13.Mode=CTS_RTS
PB13.Signal=USART3_CTS
PB14.GPIOParameters=GPIO_Label
PB14.GPIO_Label=DRIBBLER_USART3_RTS
PB14.Mode=CTS_RTS
PB14.Signal=USART3_RTS
PB15.GPIOParameters=GPIO_Label
PB15.GPIO_Label=HV_CHARGE
PB15.Signal=GPIO_Output
PB2.Signal=OPAMP3_VINM
PB3.GPIOParameters=GPIO_Label
PB3.GPIO_Label=BALL_SENSE_RST
PB3.Signal=GPIO_Output
PB5.GPIOParameters=GPIO_Label
PB5.GPIO_Label=USR_BTN
PB5.Signal=GPIO_Input
PB6.GPIOParameters=GPIO_Label
PB6.GPIO_Label=LED_SHUTDOWN_INITIATED
PB6.Signal=GPIO_Output
PB7.Mode=I2C
PB7.Signal=I2C1_SDA
PB8-BOOT0.GPIOParameters=GPIO_Label
PB8-BOOT0.GPIO_Label=BOOT0
PB8-BOOT0.Signal=GPIO_Input
PB9.GPIOParameters=GPIO_Label
PB9.GPIO_Label=LED_GREEN
PB9.Signal=GPIO_Output
PC0.GPIOParameters=GPIO_Label
PC0.GPIO_Label=BBL_AGPIO
PC0.Mode=IN6-Single-Ended
PC0.Signal=ADC1_IN6
PC1.GPIOParameters=GPIO_Label
PC1.GPIO_Label=BBC_AGPIO
PC1.Mode=IN7-Single-Ended
PC1.Signal=ADC1_IN7
PC10.GPIOParameters=GPIO_Label
PC10.GPIO_Label=I2C1_RST
PC10.Signal=GPIO_Output
PC11.GPIOParameters=GPIO_Label
PC11.GPIO_Label=I2C1_nDET
PC11.Signal=GPIO_Input
PC12.GPIOParameters=GPIO_Label
PC12.GPIO_Label=I2C1_INT
PC12.Signal=GPIO_Input
PC14-OSC32_IN.Mode=LSE-External-Oscillator
PC14-OSC32_IN.Signal=RCC_OSC32_IN
PC15-OSC32_OUT.Mode=LSE-External-Oscillator
PC15-OSC32_OUT.Signal=RCC_OSC32_OUT
PC2.GPIOParameters=GPIO_Label
PC2.GPIO_Label=BBR_AGPIO
PC2.Mode=IN8-Single-Ended
PC2.Signal=ADC1_IN8
PC3.GPIOParameters=GPIO_Label
PC3.GPIO_Label=VHV_SENSE
PC3.Mode=IN9-Single-Ended
PC3.Signal=ADC1_IN9
PC6.Mode=I2C
PC6.Signal=I2C4_SCL
PC7.Mode=I2C
PC7.Signal=I2C4_SDA
PC8.Mode=I2C
PC8.Signal=I2C3_SCL
PC9.Mode=I2C
PC9.Signal=I2C3_SDA
PD0.GPIOParameters=GPIO_Label
PD0.GPIO_Label=DIP0
PD0.Signal=GPIO_Input
PD1.GPIOParameters=GPIO_Label
PD1.GPIO_Label=DIP1
PD1.Signal=GPIO_Input
PD10.GPIOParameters=GPIO_Label
PD10.GPIO_Label=I2C4_INT
PD10.Signal=GPIO_Input
PD11.GPIOParameters=GPIO_Label
PD11.GPIO_Label=I2C4_nDET
PD11.Signal=GPIO_Input
PD12.GPIOParameters=GPIO_Label
PD12.GPIO_Label=I2C4_RST
PD12.Signal=GPIO_Output
PD13.GPIOParameters=GPIO_Label
PD13.GPIO_Label=I2C3_INT
PD13.Signal=GPIO_Input
PD14.GPIOParameters=GPIO_Label
PD14.GPIO_Label=I2C3_nDET
PD14.Signal=GPIO_Input
PD15.GPIOParameters=GPIO_Label
PD15.GPIO_Label=I2C3_RST
PD15.Signal=GPIO_Output
PD2.GPIOParameters=GPIO_Label
PD2.GPIO_Label=DIP2
PD2.Signal=GPIO_Input
PD3.GPIOParameters=GPIO_Label
PD3.GPIO_Label=BALL_SENSE_USART2_CTS
PD3.Mode=CTS_RTS
PD3.Signal=USART2_CTS
PD4.GPIOParameters=GPIO_Label
PD4.GPIO_Label=BALL_SENSE_USART2_RTS
PD4.Mode=CTS_RTS
PD4.Signal=USART2_RTS
PD5.GPIOParameters=GPIO_Label
PD5.GPIO_Label=BALL_SENSE_USART2_TX
PD5.Mode=Asynchronous
PD5.Signal=USART2_TX
PD6.GPIOParameters=GPIO_Label
PD6.GPIO_Label=BALL_SENSE_USART2_RX
PD6.Mode=Asynchronous
PD6.Signal=USART2_RX
PD7.GPIOParameters=GPIO_Label
PD7.GPIO_Label=BALL_SENSE_BOOT0
PD7.Signal=GPIO_Output
PD8.GPIOParameters=GPIO_Label
PD8.GPIO_Label=HV_CHIP
PD8.Signal=GPIO_Input
PD9.GPIOParameters=GPIO_Label
PD9.GPIO_Label=HV_KICK
PD9.Signal=GPIO_Output
PE0.GPIOParameters=GPIO_Label
PE0.GPIO_Label=LED_RED
PE0.Signal=GPIO_Output
PE1.GPIOParameters=GPIO_Label
PE1.GPIO_Label=LED_BLUE
PE1.Signal=GPIO_Output
PE10.GPIOParameters=GPIO_Label
PE10.GPIO_Label=VSW_EN
PE10.Signal=GPIO_Output
PE11.GPIOParameters=GPIO_Label
PE11.GPIO_Label=VSW_PGOOD
PE11.Signal=GPIO_Input
PE13.GPIOParameters=GPIO_Label
PE13.GPIO_Label=DRIBBLER_BOOT0
PE13.Signal=GPIO_Output
PE14.GPIOParameters=GPIO_Label
PE14.GPIO_Label=DRIBBLER_RST
PE14.Signal=GPIO_Output
PE15.GPIOParameters=GPIO_Label
PE15.GPIO_Label=DRIBBLER_USART3_RX
PE15.Mode=Asynchronous
PE15.Signal=USART3_RX
PE2.GPIOParameters=GPIO_Label
PE2.GPIO_Label=DOTSTAR_SPI4_SCK
PE2.Mode=Full_Duplex_Master
PE2.Signal=SPI4_SCK
PE3.GPIOParameters=GPIO_Label
PE3.GPIO_Label=DOTSTAR_SPI4_NSS
PE3.Mode=NSS_Signal_Hard_Input
PE3.Signal=SPI4_NSS
PE4.GPIOParameters=GPIO_Label
PE4.GPIO_Label=DIP3
PE4.Signal=GPIO_Output
PE5.GPIOParameters=GPIO_Label
PE5.GPIO_Label=DOTSTAR_SPI4_MISO
PE5.Mode=Full_Duplex_Master
PE5.Signal=SPI4_MISO
PE6.GPIOParameters=GPIO_Label
PE6.GPIO_Label=DOTSTAR_SPI4_MOSI
PE6.Mode=Full_Duplex_Master
PE6.Signal=SPI4_MOSI
PE8.GPIOParameters=GPIO_Label
PE8.GPIO_Label=USR_ADJ1
PE8.Mode=IN6-Single-Ended
PE8.Signal=ADC3_IN6
PE9.GPIOParameters=GPIO_Label
PE9.GPIO_Label=USR_ADJ2
PE9.Mode=IN2-Single-Ended
PE9.Signal=ADC3_IN2
PF0-OSC_IN.Mode=HSE-External-Oscillator
PF0-OSC_IN.Signal=RCC_OSC_IN
PF1-OSC_OUT.Mode=HSE-External-Oscillator
PF1-OSC_OUT.Signal=RCC_OSC_OUT
PG10-NRST.GPIOParameters=GPIO_Label
PG10-NRST.GPIO_Label=NRST
PG10-NRST.Signal=GPIO_Input
RCC.HSE_VALUE=8000000
RCC.SYSCLKFreq_VALUE=16000000
board=custom

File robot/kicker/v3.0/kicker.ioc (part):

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Mcu.Name=STM32F411R(C-E)Tx
Mcu.Package=LQFP64
Mcu.UserName=STM32F411RETx
PA0-WKUP.GPIOParameters=GPIO_Label
PA0-WKUP.GPIO_Label=USART2_BOOT0_DRIB
PA0-WKUP.Signal=GPIO_Output
PA1.GPIOParameters=GPIO_Label
PA1.GPIO_Label=USART2_RST_DRIB
PA1.Signal=GPIO_Output
PA10.GPIOParameters=GPIO_Label
PA10.GPIO_Label=USART1_RX_BOOT
PA10.Mode=Asynchronous
PA10.Signal=USART1_RX
PA11.GPIOParameters=GPIO_Label
PA11.GPIO_Label=SERVO_LIM1
PA11.Signal=GPIO_Input
PA12.GPIOParameters=GPIO_Label
PA12.GPIO_Label=SERVO_LIM2
PA12.Signal=GPIO_Input
PA13.Mode=Serial_Wire
PA13.Signal=SYS_JTMS-SWDIO
PA14.Mode=Serial_Wire
PA14.Signal=SYS_JTCK-SWCLK
PA15.GPIOParameters=GPIO_Label
PA15.GPIO_Label=DET_DRIB
PA15.Signal=GPIO_Input
PA2.GPIOParameters=GPIO_Label
PA2.GPIO_Label=USART2_TX_DRIB
PA2.Mode=Asynchronous
PA2.Signal=USART2_TX
PA3.GPIOParameters=GPIO_Label
PA3.GPIO_Label=USART2_RX_DRIB
PA3.Mode=Asynchronous
PA3.Signal=USART2_RX
PA4.GPIOParameters=GPIO_Label
PA4.GPIO_Label=SPI1_NSS_FLASH
PA4.Mode=NSS_Signal_Hard_Output
PA4.Signal=SPI1_NSS
PA5.GPIOParameters=GPIO_Label
PA5.GPIO_Label=SPI1_SCK_FLASH
PA5.Mode=Full_Duplex_Master
PA5.Signal=SPI1_SCK
PA6.GPIOParameters=GPIO_Label
PA6.GPIO_Label=SPI_MISO_FLASH
PA6.Mode=Full_Duplex_Master
PA6.Signal=SPI1_MISO
PA7.GPIOParameters=GPIO_Label
PA7.GPIO_Label=SPI1_MOSI_FLASH
PA7.Mode=Full_Duplex_Master
PA7.Signal=SPI1_MOSI
PA8.GPIOParameters=GPIO_Label
PA8.GPIO_Label=SERVO_CS
PA8.Signal=GPIO_Output
PA9.GPIOParameters=GPIO_Label
PA9.GPIO_Label=USART1_TX_BOOT
PA9.Mode=Asynchronous
PA9.Signal=USART1_TX
PB0.GPIOParameters=GPIO_Label
PB0.GPIO_Label=CMD_KICK
PB0.Signal=S_TIM3_CH3
PB1.GPIOParameters=GPIO_Label
PB1.GPIO_Label=CMD_CHIP
PB1.Signal=S_TIM3_CH4
PB10.GPIOParameters=GPIO_Label
PB10.GPIO_Label=BB_RST
PB10.Signal=GPIO_Output
PB12.GPIOParameters=GPIO_Label
PB12.GPIO_Label=DIP0
PB12.Signal=GPIO_Input
PB13.GPIOParameters=GPIO_Label
PB13.GPIO_Label=DIP1
PB13.Signal=GPIO_Input
PB14.GPIOParameters=GPIO_Label
PB14.GPIO_Label=DIP2
PB14.Signal=GPIO_Input
PB15.GPIOParameters=GPIO_Label
PB15.GPIO_Label=DIP3
PB15.Signal=GPIO_Input
PB2.GPIOParameters=GPIO_Label
PB2.GPIO_Label=CMD_CHG
PB2.Signal=GPIO_Output
PB3.GPIOParameters=GPIO_Label
PB3.GPIO_Label=USR_BTN
PB3.Signal=GPIO_Input
PB4.GPIOParameters=GPIO_Label
PB4.GPIO_Label=PWR_BTN_PRESSED
PB4.Signal=GPIO_Input
PB5.GPIOParameters=GPIO_Label
PB5.GPIO_Label=PWR_KILL
PB5.Signal=GPIO_Output
PB6.GPIOParameters=GPIO_Label
PB6.GPIO_Label=I2C1_SCL_BB
PB6.Mode=I2C
PB6.Signal=I2C1_SCL
PB7.GPIOParameters=GPIO_Label
PB7.GPIO_Label=I2C_SDA_BB
PB7.Mode=I2C
PB7.Signal=I2C1_SDA
PB8.GPIOParameters=GPIO_Label
PB8.GPIO_Label=TIM10_CH1_BB_TX
PB8.Signal=S_TIM10_CH1
PB9.GPIOParameters=GPIO_Label
PB9.GPIO_Label=BB_LED_BLUE
PB9.Signal=GPIO_Output
PC0.GPIOParameters=GPIO_Label
PC0.GPIO_Label=Vref_HV
PC0.Signal=ADCx_IN10
PC1.GPIOParameters=GPIO_Label
PC1.GPIO_Label=Vref_12
PC1.Signal=ADCx_IN11
PC10.GPIOParameters=GPIO_Label
PC10.GPIO_Label=SPI3_SCK_DOTSTAR
PC10.Mode=Simplex_Bidirectional_Master
PC10.Signal=SPI3_SCK
PC11.GPIOParameters=GPIO_Label
PC11.GPIO_Label=SENSE_DET
PC11.Signal=GPIO_Output
PC12.GPIOParameters=GPIO_Label
PC12.GPIO_Label=SPI_MOSI_DOTSTAR
PC12.Mode=Simplex_Bidirectional_Master
PC12.Signal=SPI3_MOSI
PC13-ANTI_TAMP.GPIOParameters=GPIO_Label
PC13-ANTI_TAMP.GPIO_Label=LED_RED
PC13-ANTI_TAMP.Signal=GPIO_Output
PC14-OSC32_IN.Mode=LSE-External-Clock-Source
PC14-OSC32_IN.Signal=RCC_OSC32_IN
PC15-OSC32_OUT.GPIOParameters=GPIO_Label
PC15-OSC32_OUT.GPIO_Label=HI-Z
PC15-OSC32_OUT.Mode=LSE-External-Clock-Source
PC15-OSC32_OUT.Signal=RCC_OSC32_OUT
PC2.GPIOParameters=GPIO_Label
PC2.GPIO_Label=Vref_5
PC2.Signal=ADCx_IN12
PC3.GPIOParameters=GPIO_Label
PC3.GPIO_Label=Vref_6.2
PC3.Signal=ADCx_IN13
PC4.GPIOParameters=GPIO_Label
PC4.GPIO_Label=BB_RX
PC4.Signal=ADCx_IN14
PC5.GPIOParameters=GPIO_Label
PC5.GPIO_Label=TEMP_PROBE
PC5.Signal=ADCx_IN15
PC6.GPIOParameters=GPIO_Label
PC6.GPIO_Label=USART6_TX_SENSE
PC6.Mode=Asynchronous
PC6.Signal=USART6_TX
PC7.GPIOParameters=GPIO_Label
PC7.GPIO_Label=USART6_RX_SENSE
PC7.Mode=Asynchronous
PC7.Signal=USART6_RX
PC8.GPIOParameters=GPIO_Label
PC8.GPIO_Label=USART6_RST_SENSE
PC8.Signal=GPIO_Output
PC9.GPIOParameters=GPIO_Label
PC9.GPIO_Label=USART6_BOOT0_SENSE
PC9.Signal=GPIO_Output
PD2.GPIOParameters=GPIO_Label
PD2.GPIO_Label=LED_GREEN
PD2.Signal=GPIO_Output
PH0\ -\ OSC_IN.GPIOParameters=GPIO_Label
PH0\ -\ OSC_IN.GPIO_Label=CLK_8MHZ_SE
PH0\ -\ OSC_IN.Mode=HSE-External-Clock-Source
PH0\ -\ OSC_IN.Signal=RCC_OSC_IN
PH1\ -\ OSC_OUT.GPIOParameters=GPIO_Label
PH1\ -\ OSC_OUT.GPIO_Label=HI-Z
PH1\ -\ OSC_OUT.Mode=HSE-External-Clock-Source
PH1\ -\ OSC_OUT.Signal=RCC_OSC_OUT
RCC.HSE_VALUE=25000000
RCC.SYSCLKFreq_VALUE=16000000
board=custom

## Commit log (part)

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2022-11-20 Lib update
2022-11-22 fix docs for setup, initial kicker passives calc script
2022-11-29 Update schematics; initial PoC layout & routing
2022-11-29 Sync
2022-12-03 added 3751 calc script and spice
2022-12-03 add 10A and 10A with leakage models
2022-12-03 Configured for DeltaVDrain in the 5 to 80V range
2022-12-03 Configured for DeltaVDrain in the 2.5 to 50V range
2022-12-04 40A charge model converges
2022-12-04 update control board with STSPIN32F0B model
2022-12-06 added STM32H723ZGT6 schematic symbol
2022-12-09 Lib Sync
2022-12-09 Alpha (0.0.0)
2022-12-09 Minor aesthetics update; added 4 Green/Red LEDs for the dot pattern preview
2022-12-09 Hole size change for a looser tolerance fit
2022-12-10 Added background colors to symbols
2022-12-11 Minor updates
2022-12-12 Post-review updates
2022-12-15 Prepare files for production
2022-12-18 add conversion regression
2023-01-17 Prelim qualification kicker schematic
2023-01-19 Bodge Bot Kicker
2023-01-20 radio work
2023-01-27 kicker work
2023-01-28 flyback charger
2023-01-28 solenoid discharge page
2023-01-28 added IO and power
2023-01-29 Fixed pad size
2023-01-29 initial schematic complete
2023-01-30 schematic rework, add ball sense and WSD
2023-01-30 some footprint work
2023-01-31 footprint + connectors
2023-01-31 Finished footprint for radio
2023-01-31 footprint work
2023-02-01 footprint assignment complete
2023-02-01 kicker stuff
2023-02-04 first layout
2023-02-04 significant 3751 layout improvements
2023-02-04 annotate schematic with alt fet
2023-02-04 initial control pinmap
2023-02-04 add debug to pinout
2023-02-04 add early shutdown hardware line
2023-02-04 update IGBT choice
2023-02-05 New radio part schematic and updates
2023-02-05 Schematic done
2023-02-05 layout work
2023-02-06 kicker routing progress
2023-02-07 routing work
2023-02-08 Few kicker routing change
2023-02-09 kicker passing ERC, LVS, and DRC
2023-02-09 updated mounting holes to have metal pads
2023-02-09 silkscreen improvements
2023-02-09 visibility
2023-02-09 Control schematic (sans crystal oscillators)
2023-02-09 Cleanup work
2023-02-10 Updated title block & page numbers
2023-02-10 Words
2023-02-10 imu-breakout
2023-02-13 JLC fab products
2023-02-13 passing DRC
2023-02-17 addressed design review feedback, passes erc
2023-02-17 footprint selection done
2023-02-17 pcb wip
2023-02-21 Done with routing
2023-02-22 Control v1.0.0
2023-02-24 Radio PCB passes DRC
2023-02-24 Minor changes
2023-02-28 Swap IMU to new connector
2023-03-05 PCB uploaded to JLCPCB
2023-03-27 Radio cable adapter
2023-03-29 retire kicker v1.0.0, initialize kicker v1.1.0
2023-03-29 address initial issues with v1.0.0
2023-03-29 fix silkscreen DRC warning on Kicker v1.1.0
2023-04-05 clear ERC on IMU breakout
2023-04-05 imu updates and gerbers
2023-04-21 kicker fixes, 1.1.0 tssop variant
2023-04-21 update change log for v1.1.0 FE
2023-04-24 NEED KCv7.1 DRC check - silk and redundant routing fixed, v7.0
2023-04-24 NEED v7.1 DRC CHECK - change default charge mode
2023-04-24 added configurable interrupt connections, reduced profile
2023-04-25 add production files
2023-05-02 Adding jlcpcb files
2023-05-02 radio v1.0.1 - fix LED footprint, add CTS/RTS solder mux
2023-05-03 radio v1.0.1 updates
2023-05-07 Encoder Board v1.1.0
2023-05-24 lt3757 SPICE model
2023-05-24 kicker v2.0.0 proto
2023-05-25 Initial breakbeam design
2023-05-25 More transmitter changes
2023-05-26 Control v1.1.0
2023-05-26 resistor value tweak
2023-05-26 updated git ignore
2023-05-26 small resistor tweak
2023-05-27 added fet gate current lim resistor to model
2023-05-28 snubber 50A model with updated diode
2023-05-28 Diode & Rsense update; minor ERC fixes
2023-05-28 Update LCSC part number
2023-05-28 Updated Rsense LCSC part number
2023-05-29 Consolidate 4.7uF capacitor variants into one BoM item
2023-05-29 Mechanical iteration, electrical review
2023-05-29 Mechanical step files
2023-05-29 Ordering changes
2023-05-29 Fixed back resistor value
2023-06-15 Added new emitter
2023-06-19 Added VN7050AS
2023-06-19 Started switch-mod v1.0.0
2023-06-20 Power Entry Sim
2023-07-27 readme updates, soldering guide, and errata for comp 2023 release
2023-07-27 add soldering documentation
2023-07-28 nonlinear control power model
2023-07-28 update snubber
2023-09-29 kicker v3.0 work
2023-10-01 power front end work
2023-10-02 added eCAD and Python-lite dev shells
2023-10-04 added fixed python dependency, added tl3504 components script
2023-10-04 initial power on kicker v3.0
2023-10-04 update schematic to reflect spice sim
2023-10-04 update switching frequency
2023-10-04 add recommended extensions
2023-10-04 top level schematic work
2023-10-22 pinout bus for angled kicker
2023-10-27 connector work
2023-11-02 kicker v3.0 digital schematic work
2023-11-04 lots of ERC work
2023-11-08 kicker v3.0 passing ERC
2023-11-10 kicker v3.0 footprint work
2023-11-10 added inductor footprints
2023-11-14 kicker v3.0 ready for review
2023-11-17 component/footprint swaps, layout work
2023-11-21 kicker v3.0 layout work
2023-11-22 fix HV net class spacing rules
2023-11-28 breakbeam v1.2
2023-11-28 minor receiver update
2023-12-04 kicker v3.0 changes from design review
2023-12-06 add inductor footprint updates
2023-12-09 add stm32f404 100pin pinout
2023-12-21 updating schematic to stm32f407 100pin
2023-12-21 lots of kicker work
2023-12-22 kicker layout work
2023-12-22 kicker v3.0 rough placement complete
2023-12-23 kicker v3.0 routing work
2024-01-09 kicker v3.0 is ERC/DRC clean
2024-01-10 minor design review feedback, passing LVS/DRC
2024-01-10 fix ID silk, passing LVS/DRC
2024-01-13 BoM work
2024-02-13 change case mounting holes
2024-02-14 git exclude JLCPCB plugin backups
2024-02-24 finished BoM
2024-02-29 Convert to generic models
2024-02-29 Added TPS54260DGQ & TPS54561DPR
2024-02-29 Added +V_{FAN}
2024-03-03 Lib updates
2024-03-03 Control V2 Schematic Complete
2024-04-21 kicker fixes
2024-04-23 Control v2.0 pre minor mods for manufacturing
2024-04-23 Only ignore gerber/ & production_files/
2024-04-23 Push project.db
2024-04-25 fix 3-D model orientation
2024-04-25 Fix connector part number
2024-04-25 Control v2.0 for DFM review
2024-04-27 Minor routing tweaks
2024-04-27 Generate STEP
2024-05-05 update kicker pinout for next rev
2024-05-05 Minor silkscreen update
2024-05-05 Include control v1 project.db
2024-05-05 Control v2.0 pinmap
2024-05-05 Update title block
2024-05-05 Added courtyard & 3-D model
2024-05-05 Centered grid origin, updated footprints, and exported CAD model
2024-05-23 Start Kicker v3.1
2024-05-24 Update power entry and regulation
2024-05-24 Add high side switch for Vsense
2024-05-24 Swap TX/RX through isolator
2024-05-24 Add local crystals
2024-06-09 Kicker v3.1 preliminary
2024-06-11 Kicker v3.1
2024-06-11 Experimental Midplate
2024-07-31 cleanup to mark comp-2024 release
2024-07-31 remove old kicker
2024-08-01 initial commit of motor-controller
2024-08-02 initial commit of power pinout and power files
2024-08-07 battery monitor calcs
2024-08-10 update resistor values
2024-08-10 initial power board front end
2024-08-10 power schematic work
2024-08-16 power board work
2024-09-04 update inductors
2024-11-01 passing ERC, footprint work
2024-11-04 power board passing ERC/import
2024-11-04 fix bus aliasing issues
2024-11-04 swap power fets
2024-11-04 added latest SOA calcs
2024-11-06 make 5V local supply switch mode
2024-11-06 add enable pull downs on regulator enables
2024-11-15 fix 5V local AGAIN
2024-11-15 fix power flag ERC conflict
2024-11-15 initial placement
2024-11-15 Revert "Merge branch 'main' of github.com:SSL-A-Team/electrical"
    This reverts commit e3e905e086ad656dbe27eb1d7768ff8b77b20f23, reversing
    changes made to b918b4ecffb897a591c7a6949e309c7e6ea46d1e. Merge broke
    schematics.
2024-11-22 First pass at schematic and pinout
2024-11-22 Move files
2024-11-23 add DMA allocation to pinout file
2024-11-23 fix PASS 1x06
2024-11-24 Omni wheel cover plate
2024-11-24 Schematic feedback
2024-11-26 kicker power rework
2024-11-30 remove 12v0 supply
2024-12-01 WIP Layout
2024-12-02 power board layout work
2024-12-02 Finish switch to G0 and larger space
2024-12-02 Move cubemx files around
2024-12-02 Optical flow routing
2024-12-04 Submitted JLCPCB order
2024-12-05 power v1 passing DRC
2024-12-05 sch passing ERC
2024-12-06 Add DF45M024053-A2
2024-12-07 Kicker - partial component placement
2024-12-07 motor controller passing ERC
2024-12-07 add connector libs
2024-12-16 motor controller routing progress
2024-12-17 motor controller layout updates
2024-12-18 motor controller passing DRC
2024-12-19 add bulk C to mc
2024-12-20 MC layout done
2024-12-20 spice model of current sense
2024-12-20 update gitignore
2024-12-20 add WireViz deps
2024-12-20 add power wiring harness diagram, add current sense cals
2024-12-20 update current sense calcs
2024-12-20 update values in current sense spice sim and reflect in schematic
2024-12-20 minor lt spice sch tweak :
2024-12-20 update sch values on PCB
2024-12-23 initial commit of control v3
2024-12-28 add TVS, update fusing, remove LDO body diode
2024-12-28 remove TLV 3v0 body diode, update 3v0 fusing
2024-12-28 update fusing and remove diode on 3v0 supply
2024-12-29 pinout done
2024-12-30 control v3 passing ERC
2024-12-30 connector style touchups
2024-12-30 update boot mode docs, schematic visual fixes, UART default state fixes
2024-12-30 footprint selection done, placement work
2025-01-20 fix power output connector and 3v3 local en pullup
2025-01-20 minor motor control updates before fab
2025-01-20 make battery balance connector GND Hi-Z
2025-01-22 very coarse control placement
2025-01-22 initial coase placement done
2025-01-25 load board config and profiles
2025-01-26 Initial decoupling caps and some resistor placement
2025-01-26 Placing and routing capacitors near control MCU
2025-01-26 control routing/placement work
2025-01-27 Resistor placement for motors
2025-01-28 Some motor and connector routing
2025-01-29 fix SD pinout, routing work
2025-02-01 control routing work
2025-02-08 control v3 passing DRC
2025-02-16 control v3 ordered
2025-02-16 coarse kicker placement done
2025-02-16 power v1.1 initial load
2025-02-16 motor controller v1.0 prod artifacts
2025-03-02 kicker routing worK
2025-03-02 kicker passing DRC
2025-03-11 power v1.1 layout work
2025-03-13 Adjust for mechanical constraints and route board
2025-03-13 Update schematic with updated symbol to resolve ERC
2025-03-13 Update values
2025-03-13 Set preferred bank capacitor PN
2025-03-13 Update potentiometer values
2025-03-14 power layout work
2025-03-17 power work
2025-03-17 fixed old conenctors
2025-03-17 update stm ide pinout
2025-03-17 layout after connector fix done
2025-03-17 add prod files
2025-03-21 Update USB
2025-03-30 kicker v4.0 prod files
2025-04-01 power v1.1 prod files
2025-04-01 add jtag connector
2025-04-06 power v1.1. final prod files
2025-04-08 fix hall silk on motor controller
2025-04-08 fix xt30 and vertical data connector on schemnatic
2025-04-13 update radio KiCad 8.0, reprod files
2025-04-13 control v3.0 updated prod files
2025-04-18 fixed to kicker v4
2025-04-18 pull back HV plane by cutout
2025-04-18 add GND patch pads
2025-04-18 kicker v4 prod files
2025-04-28 Breakbeam tx with new footprint
2025-05-03 Finished emitter
2025-05-03 Both breakbeam boards passing drc
2025-05-07 Design review update
2025-05-07 Minor updates & STEP export
2025-05-07 Re-export STEP with Grid origin
2025-05-07 Switch connector symbol to include MP
2025-05-07 Minor routing changes
2025-05-07 Export STEP
2025-05-07 Re-export STEP
2025-07-07 Additional current sense calcs
2025-07-27 add prod files for motor controller
2025-07-27 update motor controller current sense and Vmotor protections
2025-07-28 Midplate structural PCB
2025-07-28 update 3v3 protection diode
2025-07-29 initial schematic of NORA radio
2025-07-29 assign NORA radio footprints
2025-07-30 radio layout done, JLC part numbers added
2025-08-01 motor controller v1.1 prod files
2026-01-28 fixed amplifier schematic
2026-02-14 BoM tweaks for prod
2026-03-28 BoM updated
2026-04-05 minor tweaks to pass DRC with courtyard updates, fab products
2026-04-27 update for prod
2026-05-20 Breakbeam v3.0
